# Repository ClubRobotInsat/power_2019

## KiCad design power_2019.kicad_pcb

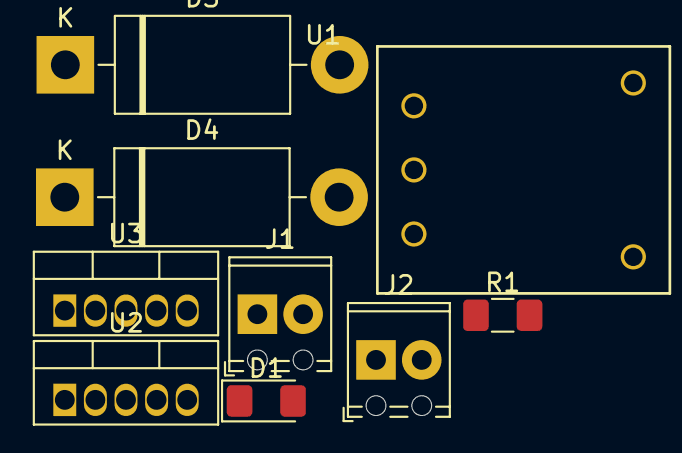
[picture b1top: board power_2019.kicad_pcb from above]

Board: 2 copper layers, 9 parts (0 on the bottom side), 5 nets, no tracks yet.

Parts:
D1: LED_12V_rouge; LED_1206_3216Metric_Pad1.42x1.75mm_HandSolder
D3, D4: 1N5822; D_DO-201AD_P15.24mm_Horizontal
J1: Alim logique; TerminalBlock_Phoenix_MPT-0,5-2-2.54_1x02_P2.54mm_Horizontal
J2: Alim puissance; TerminalBlock_Phoenix_MPT-0,5-2-2.54_1x02_P2.54mm_Horizontal
R1: 1k; R_1206_3216Metric_Pad1.42x1.75mm_HandSolder
U1: PTH08080W
U2, U3: LM2576T-ADJ; TO-220-5_Vertical

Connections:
+5V: J1.2, U1.3
GND: D1.1, D3.2, D4.2, J1.1, J2.1, U1.2, U2.3, U2.5, U3.3, U3.5
unnamed: D3.1, U2.2
unnamed: D4.1, U3.2
unnamed: D1.2, R1.2

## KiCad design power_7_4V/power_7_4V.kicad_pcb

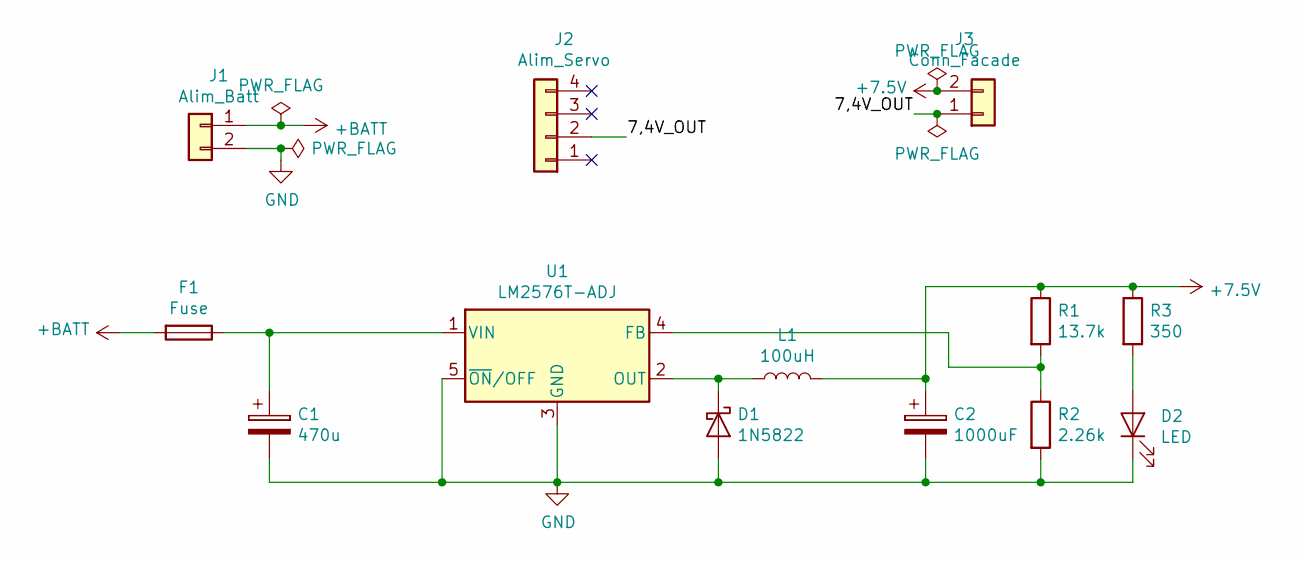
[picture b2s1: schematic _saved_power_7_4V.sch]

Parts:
C1: 470u; CP_Radial_D5.0mm_P2.50mm
C2: 1000uF; CP_Radial_D5.0mm_P2.50mm
D1: 1N5822; D_DO-201AD_P15.24mm_Horizontal
D2: LED; LED_D3.0mm
F1: Fuse; Fuse_Bourns_MF-RG300
J1: Alim_Batt; PhoenixContact_MSTBA_2,5_2-G_1x02_P5.00mm_Horizontal
J2: Alim_Servo; HE14-4-straight
J3: Conn_Facade; HE14-2-straight
L1: 100uH; L_Bourns_SDR1806
R1: 13.7k; R_Axial_DIN0207_L6.3mm_D2.5mm_P2.54mm_Vertical
R2: 2.26k; R_Axial_DIN0207_L6.3mm_D2.5mm_P2.54mm_Vertical
R3: 350; R_Axial_DIN0207_L6.3mm_D2.5mm_P2.54mm_Vertical
U1: LM2576T-ADJ; TO-220-5_Vertical

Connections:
+7.5V: C2.1, J3.2, L1.2, R1.1, R3.1
+BATT: F1.2, J1.1
/7,4V_OUT: J2.2, J3.1
GND: C1.2, C2.2, D1.2 (A), D2.1 (K), J1.2, R2.2, U1.3 (GND), U1.5 (~ON~/OFF)
unnamed: C1.1, F1.1, U1.1 (VIN)
unnamed: D1.1 (K), L1.1, U1.2 (OUT)
unnamed: D2.2 (A), R3.2
unnamed: R1.2, R2.1, U1.4 (FB)

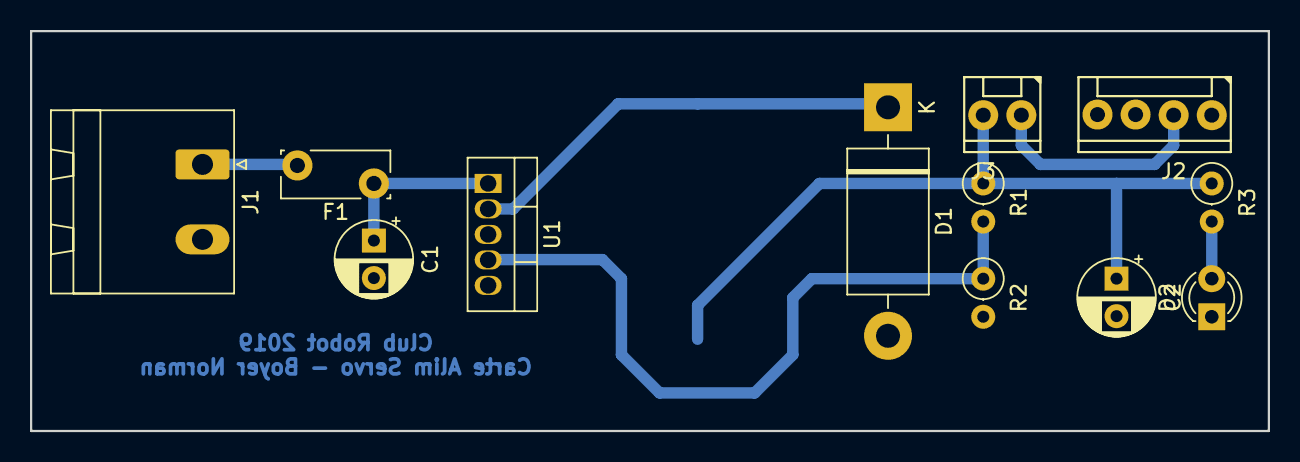
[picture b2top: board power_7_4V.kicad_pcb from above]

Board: 2 copper layers, 82.5 x 26.7 mm, 13 parts (1 on the bottom side), 8 nets.

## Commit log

2019-03-07 Carte alim
2019-03-14 maj regu 5V
2019-05-16 update power board
2019-05-23 alim moteur
2019-05-23 maj servo
